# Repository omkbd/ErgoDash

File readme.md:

# Notice

2019/5/5にファームウェアをアップデートしました。  
それ以前にハードウェアを作製されていた方はアップデートの必要はありませんが、  
アップデートした方は[ビルドガイドの最終項](https://github.com/omkbd/ErgoDash/blob/master/Doc/build.md#12-firmware%E3%81%AE%E6%9B%B8%E3%81%8D%E8%BE%BC%E3%81%BF)を参照してください。

The firmware has been updated to 5/5/2019.  
If you have previously created hardware, you do not need to update, but if you have updated, please refer to [the last section of the build guide](https://github.com/omkbd/ErgoDash/blob/master/Doc/build-en.md#12-firmware).

# ErgoDash

[Japanese Read me](https://github.com/omkbd/ErgoDash/blob/master/Doc/ergodash_jp.md)

# Layout

# Parts

[ErgoDash PCB](https://github.com/omkbd/ErgoDash/tree/master/PCB)
 × 2  
[ErgoDash Case](https://github.com/omkbd/ErgoDash/tree/master/Case)
 × 2  
Switch (MX-compatible and Alps switches are supported) × 66-70  
Keycap × 66-70  
1N4148 diode × 66-70  
Arduino Pro Micro × 2  
TRRS jack MJ-4PP-9 × 2  
MJTP1117 switch × 2  
TRRS cable × 1  
Micro USB cable × 1  
M2×5mm screw × 22  
M2×8mm screw × 6  
M2×6mm spacer × 14  
Rubber feet × 8

---Option---  
LED WS2812B × 24  
LED 3mm × 66-70  
470Ω resistor × 66-70  
1kΩ resistor × 2  
NchMOSFET IRLML6344TRPbF × 2  

# Firmware

The ErgoDash uses QMK for its firmware, and the code for it is here:
[QMK - ErgoDash directory](https://github.com/qmk/qmk_firmware/tree/master/keyboards/omkbd/ergodash)
.

# Build Guide

[Japanese Build Guide](https://github.com/omkbd/ErgoDash/blob/master/Doc/build.md)  
[English Build Guide](https://github.com/omkbd/ErgoDash/blob/master/Doc/build-en.md)

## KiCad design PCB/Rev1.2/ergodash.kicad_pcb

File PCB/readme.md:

# ErgoDash PCB

## 変更履歴

### [rev.1.1]
・圧電スピーカーを追加（試験的）  
・上記に伴うパーツの配置を調整  
・シルク表記を追加

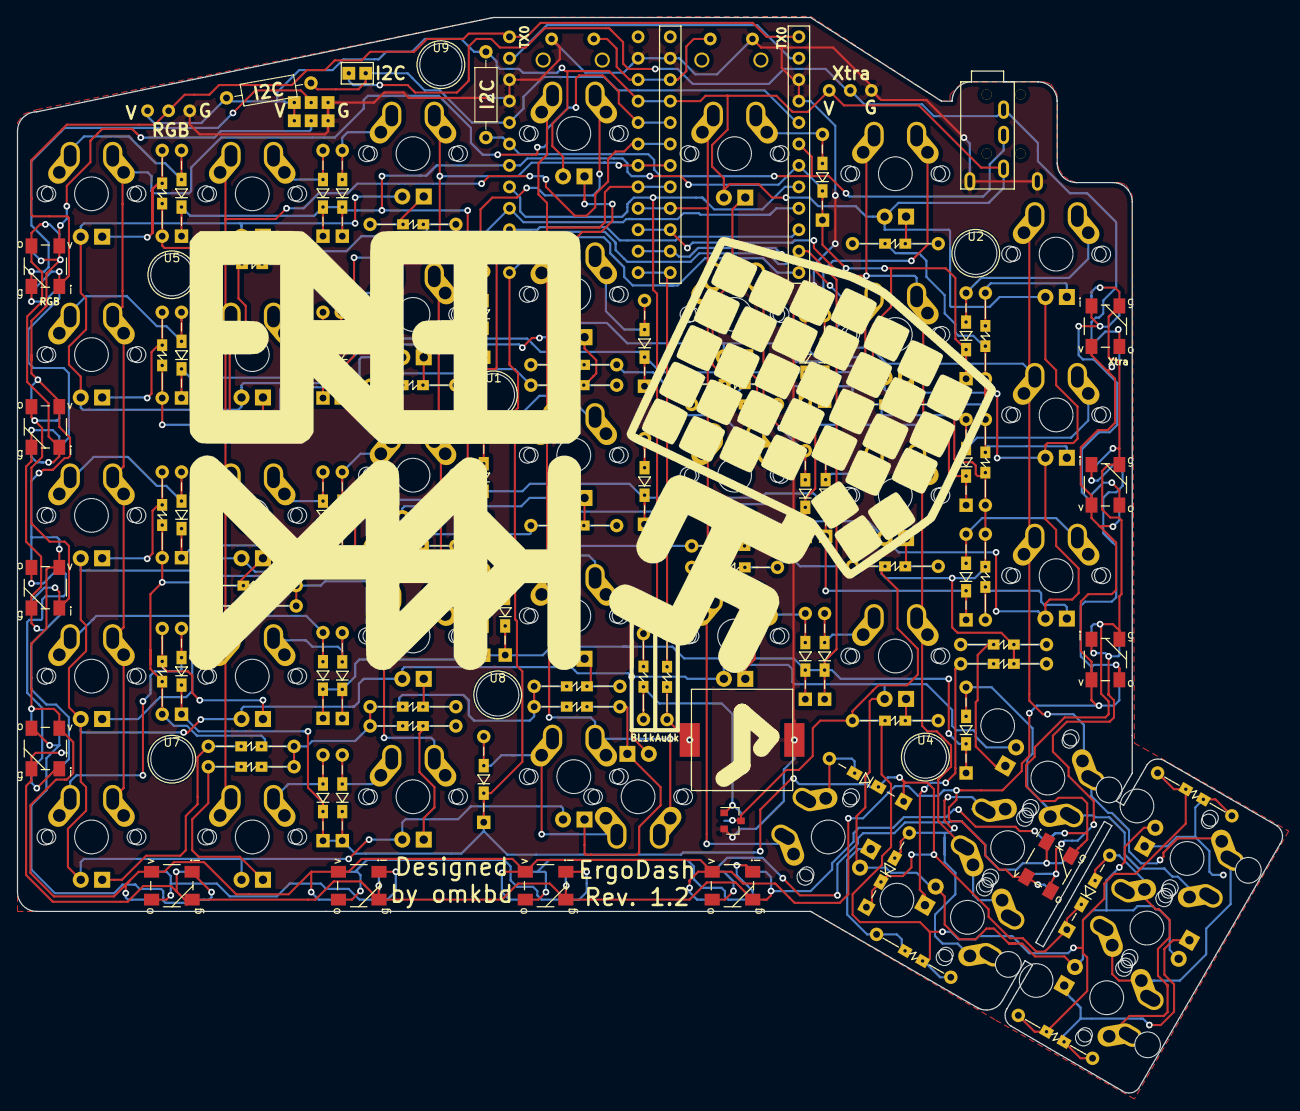
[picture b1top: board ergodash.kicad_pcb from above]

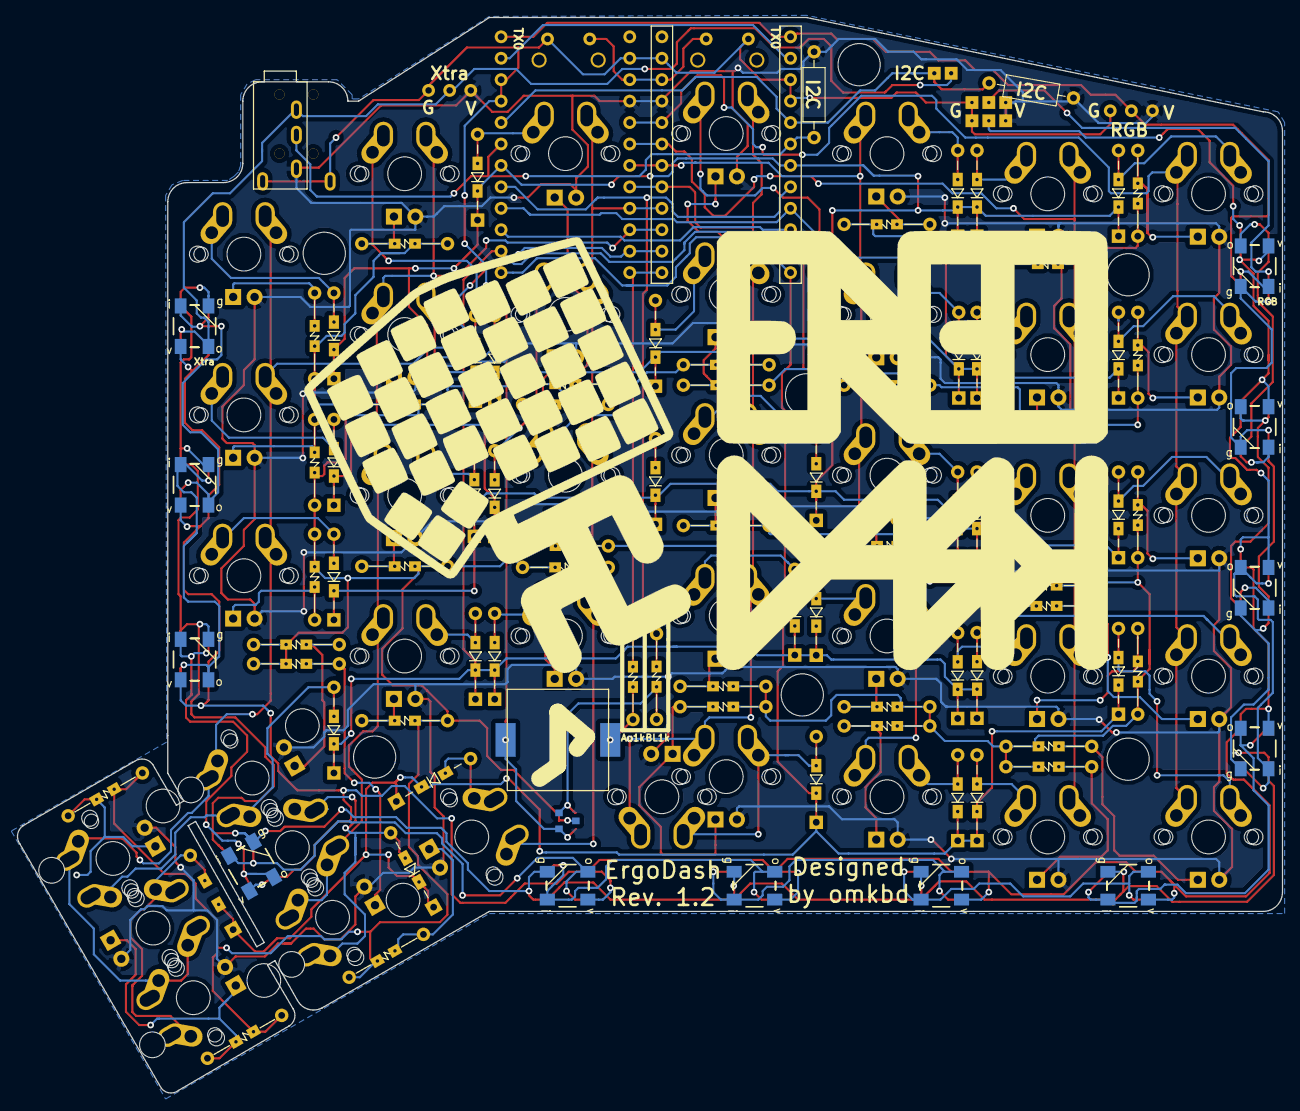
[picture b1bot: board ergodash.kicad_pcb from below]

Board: 2 copper layers, 149.9 x 127.4 mm, 183 parts (27 on the bottom side), 109 nets.

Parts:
D1, D2, D3, D4, D5, D6, D7, D8, D9, D10, D11, D12, D13, D14, D15, D16, D17, D18, D19, D20, D21, D22, D23, D24, D25, D26, D27, D28, D29, D30, D31, D32, D33, D34: D; Diode_SMD_THT3
D35, D36, D37, D38, D39, D40, D41, D42, D43, D44, D45, D46, D47, D48, D49, D50, D51, D52, D53, D54, D55, D56, D57, D58, D59, D60, D61, D62, D63, D64, D65, D66, D67, D69, D70, D71, D72, D73: LED; CHERRY_MX_LED2
D68: D; Diode_SMD_THT2
J1: 5PIN; trrs_jack2
J2, J3: Conn_01x03; conn3
J4, J5: GS3; jumper2
LED1, LED2, LED3, LED4, LED5, LED6, LED7, LED8, LED9, LED10, LED11, LED12: WS2812B; WS2812B-5
M1: Speaker; PKLCS1212E4001-R1
Q1: IRLML6344TRPbF; SOT-23_2
R1, R2: R; R_Axial_DIN0207_L6.3mm_D2.5mm_P10.16mm_Horizontal
R3, R4, R5, R6, R7, R8, R9, R10, R11, R12, R14, R15, R16, R17, R18, R19, R20, R21, R22, R23, R24, R25, R26, R27, R28, R29, R30, R31, R32, R33, R34, R35, R36, R37, R38, R39: R; Resistors_SMD_THT
R13, R40: 1k; Resistors_SMD_THT
SW1, SW2, SW3, SW4, SW5, SW6, SW7, SW8, SW9, SW10, SW11, SW12, SW13, SW14, SW15, SW16, SW17, SW18, SW19, SW20, SW21, SW22, SW23, SW24, SW25, SW26, SW27, SW28, SW30, SW31, SW32, SW33, SW34, SW35, SW36, SW38, SW39, SW40, SW41: SW_PUSH; MX_ALPS
SW29, SW37: SW_Push; tact_switch2
U1, U2, U4, U5, U7, U8, U9: HOLE; hole
U3, U6: ProMicro; ProMicro_rev
W1: jumper_smd; jumper_smd_2dub

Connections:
/Audio: R40.1, U3.8, U6.8
/Backlight: R13.1, U3.13, U6.13
/RBG: J2.2, LED1.2, U3.1, U6.1
/RX: U3.2, U6.2
/col0: SW1.1, SW2.1, SW3.1, SW4.1, SW30.1, U3.20, U6.20
/col1: SW5.1, SW6.1, SW7.1, SW8.1, SW31.1, U3.19, U6.19
/col2: SW9.1, SW10.1, SW11.1, SW12.1, SW32.1, U3.18, U6.18
/col3: SW13.1, SW14.1, SW15.1, SW16.1, SW33.1, SW38.1, U3.17, U6.17
/col4: SW17.1, SW18.1, SW19.1, SW20.1, SW34.1, U3.16, U6.16
/col5: SW21.1, SW22.1, SW23.1, SW24.1, SW35.1, SW36.1, U3.15, U6.15
/col6: SW25.1, SW26.1, SW27.1, SW28.1, SW39.1, SW40.1, SW41.1, U3.14, U6.14
/row0: D1.1, D5.1, D9.1, D13.1, D17.1, D21.1, D25.1, U3.7, U6.7
/row1: D2.1, D6.1, D10.1, D14.1, D18.1, D22.1, D26.1, U3.9, U6.9
/row2: D3.1, D7.1, D11.1, D15.1, D19.1, D23.1, D27.1, U3.10, U6.10
/row3: D4.1, D8.1, D12.1, D16.1, D20.1, D24.1, D28.1, U3.11, U6.11
/row4: D29.1, D30.1, D31.1, D32.1, D33.1, D34.1, D68.1, U3.12, U6.12
/rst: SW29.1, SW37.1, U3.22, U6.22
/scl: R1.2, U3.5, U6.5, W1.2
/sda/uart: J1.3, R2.2, U3.6, U6.6
/xtradata: J1.2, J3.2, LED12.4, W1.1
GND: J1.4, J1.5, J2.3, J3.3, J4.3, J5.3, M1.1, Q1.2, SW29.2, SW37.2, U3.3, U3.4, U3.23, U6.3, U6.4, U6.23
unnamed: D1.2, SW1.2
unnamed: D2.2, SW2.2
unnamed: D3.2, SW3.2
unnamed: D4.2, SW4.2
unnamed: D5.2, SW5.2
unnamed: D6.2, SW6.2
unnamed: D7.2, SW7.2
unnamed: D8.2, SW8.2
unnamed: D9.2, SW9.2
unnamed: D10.2, SW10.2
unnamed: D11.2, SW11.2
unnamed: D12.2, SW12.2
unnamed: D13.2, SW13.2
unnamed: D14.2, SW14.2
unnamed: D15.2, SW15.2
unnamed: D16.2, SW16.2
unnamed: D17.2, SW17.2
unnamed: D18.2, SW18.2
unnamed: D19.2, SW19.2
unnamed: D20.2, SW20.2
unnamed: D21.2, SW21.2
unnamed: D22.2, SW22.2
unnamed: D23.2, SW23.2
unnamed: D24.2, SW24.2
unnamed: D25.2, SW25.2
unnamed: D26.2, SW26.2
unnamed: D27.2, SW27.2
unnamed: D28.2, SW28.2, SW39.2
unnamed: D29.2, SW30.2
unnamed: D30.2, SW31.2
unnamed: D31.2, SW32.2
unnamed: D32.2, SW33.2, SW38.2
unnamed: D33.2, SW34.2
unnamed: D34.2, SW35.2, SW36.2
unnamed: D35.1, R3.1
unnamed: D36.1, R4.1
unnamed: D37.1, R5.1
unnamed: D38.1, R6.1
unnamed: D39.1, R7.1
unnamed: D40.1, R8.1
unnamed: D41.1, R9.1
unnamed: D42.1, R10.1
unnamed: D43.1, R11.1
unnamed: D44.1, R12.1
unnamed: D45.1, R15.1
unnamed: D46.1, R16.1
unnamed: D47.1, R17.1
unnamed: D48.1, R18.1
unnamed: D49.1, R19.1
unnamed: D50.1, R20.1
unnamed: D51.1, R21.1
unnamed: D52.1, R22.1
unnamed: D53.1, R23.1
unnamed: D54.1, R24.1
unnamed: D55.1, R25.1
unnamed: D56.1, R26.1
unnamed: D57.1, R27.1
unnamed: D58.1, R28.1
unnamed: D59.1, R29.1
unnamed: D60.1, R30.1
unnamed: D61.1, R31.1
unnamed: D62.1, R32.1
unnamed: D63.1, R33.1
unnamed: D64.1, R34.1
unnamed: D65.1, R35.1
unnamed: D66.1, D67.1, R36.1
unnamed: D68.2, SW40.2, SW41.2
unnamed: D69.1, R14.1
unnamed: D70.1, R37.1
unnamed: D71.1, R38.1
unnamed: D72.1, D73.1, R39.1
unnamed: J4.2, LED1.1, LED2.1, LED3.1, LED4.1, LED5.1, LED6.1, LED7.1, LED8.1, LED9.1, LED10.1, LED11.1, LED12.1
unnamed: J5.2, LED1.3, LED2.3, LED3.3, LED4.3, LED5.3, LED6.3, LED7.3, LED8.3, LED9.3, LED10.3, LED11.3, LED12.3
unnamed: LED1.4, LED2.2
unnamed: LED2.4, LED3.2
unnamed: LED3.4, LED4.2
unnamed: LED4.4, LED5.2
unnamed: LED5.4, LED6.2
unnamed: LED6.4, LED7.2
unnamed: LED7.4, LED8.2
unnamed: LED8.4, LED9.2
unnamed: LED9.4, LED10.2
unnamed: LED10.4, LED11.2
unnamed: LED11.4, LED12.2
unnamed: M1.2, R40.2
unnamed: Q1.1, R13.2
unnamed: Q1.3, R3.2, R4.2, R5.2, R6.2, R7.2, R8.2, R9.2, R10.2, R11.2, R12.2, R14.2, R15.2, R16.2, R17.2, R18.2, R19.2, R20.2, R21.2, R22.2, R23.2, R24.2, R25.2, R26.2, R27.2, R28.2, R29.2, R30.2, R31.2, R32.2, R33.2, R34.2, R35.2, R36.2, R37.2, R38.2, R39.2
VCC: D35.2, D36.2, D37.2, D38.2, D39.2, D40.2, D41.2, D42.2, D43.2, D44.2, D45.2, D46.2, D47.2, D48.2, D49.2, D50.2, D51.2, D52.2, D53.2, D54.2, D55.2, D56.2, D57.2, D58.2, D59.2, D60.2, D61.2, D62.2, D63.2, D64.2, D65.2, D66.2, D67.2, D69.2, D70.2, D71.2, D72.2, D73.2, J1.1, J2.1, J3.1, J4.1, J5.1, R1.1, R2.1, U3.21, U6.21

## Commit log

2018-06-30 add readme
2018-06-30 add space
2018-06-30 Add Case and PCB folder
2018-06-30 Fix URL
2018-07-01 add PCB and Case
2018-07-01 fix readme
2018-07-02 add japanese readme
2018-07-02 add spring pin
2018-07-03 180703 PCB readme
2018-08-07 add rev.1.1
2018-08-07 add build guide title
2018-08-07 add 買い物リスト
2018-08-14 add LICENSE
2018-08-30 add assembly
2018-09-16 add notice when using spring header
2018-09-16 fix pro micro camelcase
2018-09-17 fix readme
    販売情報の追加
2018-09-17 add mini readme
2018-09-17 fix mini readme
2018-09-19 add case data
2018-10-26 add mini doc
2018-10-27 add mini case data
2018-12-03 Add some detail that I was hard to make out.
2018-12-14 add stabilizer instruction
2018-12-14 it's key cap, not key top
2018-12-17 Support Rev.1.2
2018-12-17 add gerber data
2018-12-17 add kicad data
2019-02-03 Add files via upload
    Used Microsoft Translate to follow instructions and build my board. Took the translation and added notes from my build experience
2019-02-03 Update build-en.md
    minior change
2019-02-03 Update build-en.md
    formatting, spelling error
2019-02-03 Update build-en.md
    formatting
2019-02-03 Update build-en.md
    changed ref
2019-02-12 Manually translate unclear areas of automatic translation
2019-03-18 Update build-en.md
    English instruction clarifications and formatting improvements.
2019-04-25 Added a description of the qmk firmware build options for the right-handed master.
2019-05-04 最新ファームウェア用に修正
2019-05-06 update build guide jp
2019-05-06 update build guide
2019-05-12 ErgoDash mini has 20 LEDs
2019-05-12 Fix link for build guide
2019-07-11 Add precisions to the english build guide
    The side of components is specified a the beginning of the guide but not in the actual steps where it is important to know.
    Also added precision about the position of the arrow/modifier key depending of the side of the keyboard
2019-07-12 Fix typo in english doc
2020-04-13 fixed stabileser hole for 3mm aclic plate
2020-04-13 fixed stabiliser hole for 3mm aclic plate
2020-04-15 fixed ergodash-mini 2U stabiliser hole
2020-09-01 Add a notice about Underglow LEDs and Backlight LEDs.
2020-09-13 Spacers: make the English list and guide the same as the Japanese.
    Resolves #26
    Resolves #33
2020-09-13 Add rubber feet to English shopping list.
2020-10-18 [Mod] SVG ファイルの全体のサイズが 75%に拡大されいたものを変更
    Inkscape 1.0.1 にて確認と編集。
2020-11-04 [Mod] キースイッチ穴が 14.1mm 辺になる様に全体を拡大。
    ai ファイル上で適切な大きさを確認。
    また、svg ファイル上で「キースイッチ穴」の一辺が 14.1mm 前後に成る倍率で、
    拡大変形属性を各グルーブに追加。
    ただし、Ubuntu 上の Inkscape ver.1.0 での確認と編集。
2020-11-04 [Mod] `transform` 属性の値を `matrix` から `scale` へ変更
    `matrix` (変形行列)指定よりも `scale` (拡大・縮小) 指定の方が、
    今回の改良案に対しては適切と感じたため。
2021-06-06 Update build.md
    add via
2021-06-06 Update build.md
    Fix VIA
2022-05-15 Fix link: readme.md
2022-05-15 Fix link: Doc/build-en.md
2022-05-15 Fix link: Doc/build.md
2022-05-15 Fix link: Doc/ergodash_jp.md
